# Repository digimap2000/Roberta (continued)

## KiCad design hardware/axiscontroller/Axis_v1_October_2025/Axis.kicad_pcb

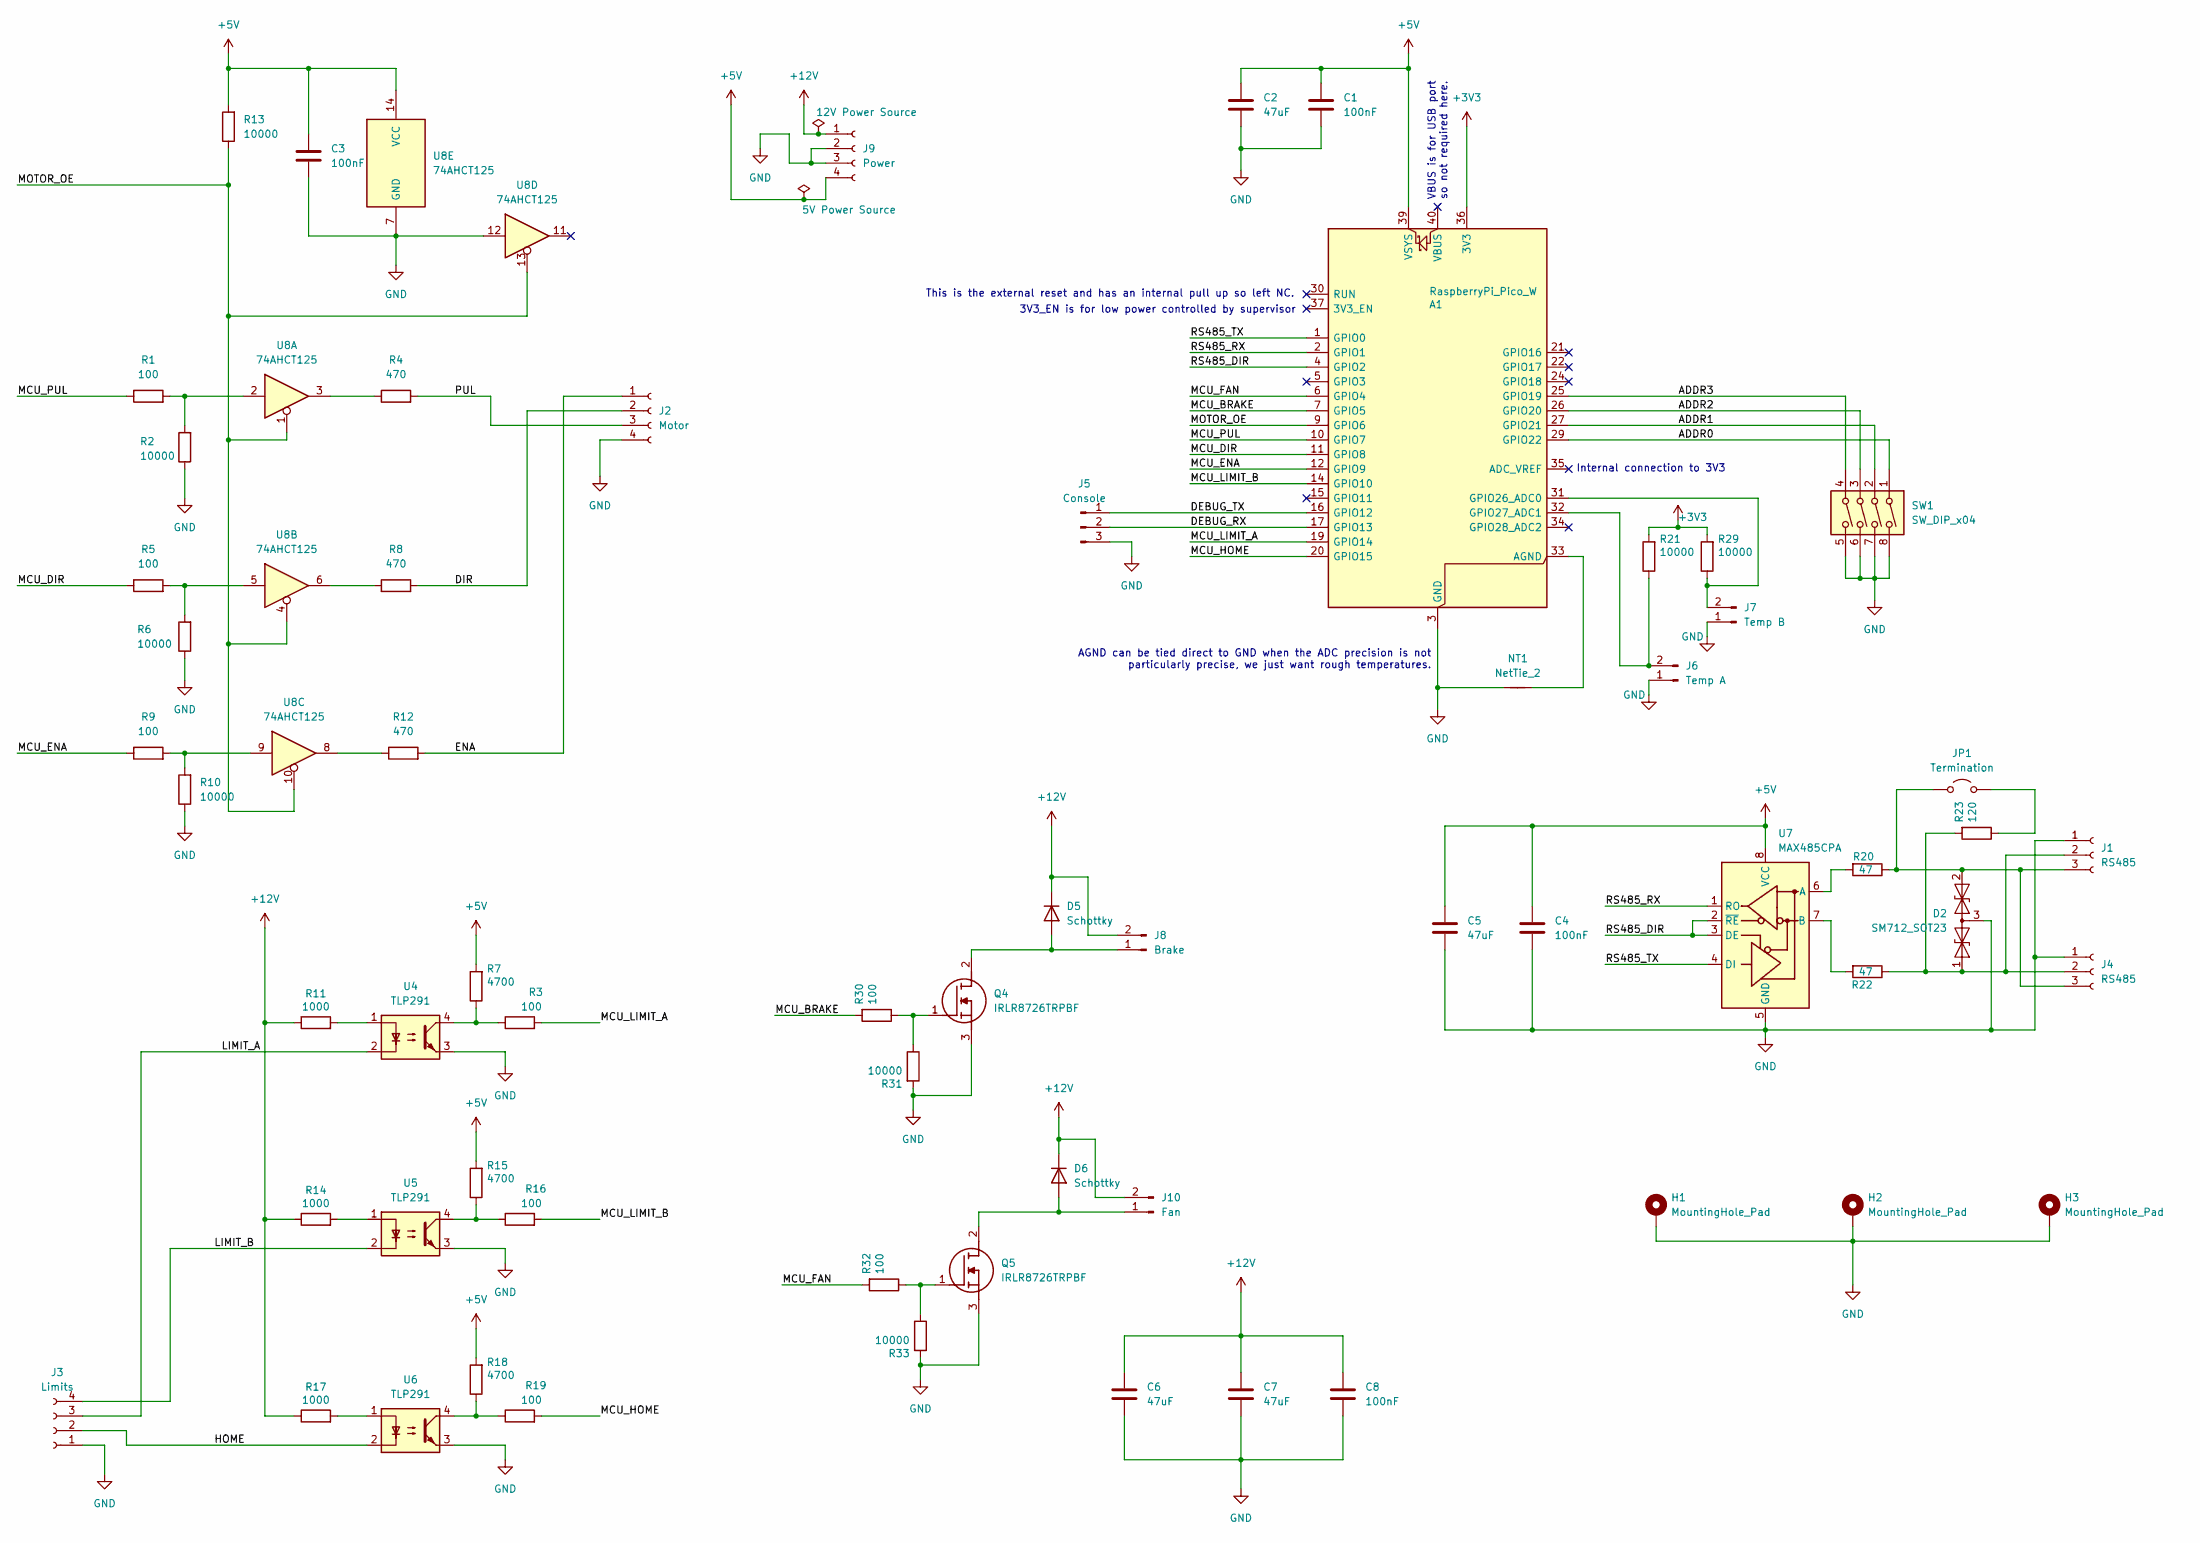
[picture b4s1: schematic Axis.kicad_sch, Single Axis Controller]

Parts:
A1: RaspberryPi_Pico_W; PI_PICO2_SOCKET
C1, C3, C4, C8: 100nF; C_0805_2012Metric; Part MC0805B104K500CT
C2, C5, C6, C7: 47uF; C_0805_2012Metric; Part GRT21BR60J476ME13L
D2: SM712_SOT23; SOT-23; Part SM712-02HTG
D5, D6: Schottky; D_SMB-SMC_Universal_Handsoldering; Part SS34
H1, H2, H3: MountingHole_Pad; MountingHole_2.2mm_M2_DIN965_Pad
J1, J4: RS485; MOLEX_SL_70553_0002; Part 70553-0002
J2: Motor; MOLEX_SL_70553_0003; Part 70553-0003
J3: Limits; MOLEX_SL_70553_0003; Part 70553-0003
J5: Console; MOLEX_SL_70553_0002; Part 70553-0002
J6: Temp A; MOLEX_SL_70553_0001; Part 70553-0001
J7: Temp B; MOLEX_SL_70553_0001; Part 70553-0001
J8: Brake; MOLEX_SL_70553_0001; Part 70553-0001
J9: Power; MOLEX-171857-0001; Part 171857-0004
J10: Fan; MOLEX_SL_70553_0001; Part 70553-0001
JP1: Termination; PinHeader_2x01_P2.54mm_Vertical
NT1: NetTie_2; NetTie-2_SMD_Pad2.0mm
Q4, Q5: IRLR8726TRPBF; Manufacturer_Part_Number IRLR8726TRPBF; Mouser Part Number 942-IRLR8726TRPBF
R1, R3, R5, R9, R16, R19, R30, R32: 100; R_0805_2012Metric_Pad1.20x1.40mm_HandSolder; Part ASC0805-100RFT5
R2, R6, R10, R13, R21, R29, R31, R33: 10000; R_0805_2012Metric_Pad1.20x1.40mm_HandSolder; Part CRGCQ0805F10K
R4, R8, R12: 470; R_0805_2012Metric_Pad1.20x1.40mm_HandSolder; Part ASC0805-470RFT5
R7, R15, R18: 4700; R_0805_2012Metric_Pad1.20x1.40mm_HandSolder; Part ASC0805-4K7FT5
R11, R14, R17: 1000; R_0805_2012Metric_Pad1.20x1.40mm_HandSolder; Part ASC0805-1K0FT5
R20, R22: 47; R_0805_2012Metric_Pad1.20x1.40mm_HandSolder; Part ASC1206-47RFT5
R23: 120; R_0805_2012Metric_Pad1.20x1.40mm_HandSolder; Part CRG0805F120R
SW1: SW_DIP_x04; DIP-8_W7.62mm; Part MCNDI-04S
U4, U5, U6: TLP291; SOIC-4_4.55x2.6mm_P1.27mm; Part TLP291(GB,SE
U7: MAX485CPA; DIP-8_W7.62mm; Part MAX485CPA+
U8: 74AHCT125; DIP-14_W7.62mm; Part SN74AHCT125N

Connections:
+3V3: A1.36 (3V3), R21.2, R29.2
+5V: A1.39 (VSYS), C1.1, C2.1, C3.1, C4.1, C5.1, J9.4, R7.2, R13.2, R15.2, R18.2, U7.8 (VCC), U8.14 (VCC)
+12V: C6.1, C7.1, C8.1, D5.1 (K), D6.1 (K), J8.2, J9.1, J10.2, R11.1, R14.1, R17.1
/ADDR0: A1.29 (GPIO22), SW1.1
/ADDR1: A1.27 (GPIO21), SW1.2
/ADDR2: A1.26 (GPIO20), SW1.3
/ADDR3: A1.25 (GPIO19), SW1.4
/DEBUG_RX: A1.17 (GPIO13), J5.2
/DEBUG_TX: A1.16 (GPIO12), J5.1
/DIR: J2.2, R8.2
/ENA: J2.1, R12.2
/HOME: J3.2, U6.2
/LIMIT_A: J3.3, U4.2
/LIMIT_B: J3.4, U5.2
/MCU_BRAKE: A1.7 (GPIO5), R30.2
/MCU_DIR: A1.11 (GPIO8), R5.1
/MCU_ENA: A1.12 (GPIO9), R9.1
/MCU_FAN: A1.6 (GPIO4), R32.2
/MCU_HOME: A1.20 (GPIO15), R19.2
/MCU_LIMIT_A: A1.19 (GPIO14), R3.2
/MCU_LIMIT_B: A1.14 (GPIO10), R16.2
/MCU_PUL: A1.10 (GPIO7), R1.1
/MOTOR_OE: A1.9 (GPIO6), R13.1, U8.1, U8.4, U8.10, U8.13
/PUL: J2.3, R4.2
/RS485_DIR: A1.4 (GPIO2), U7.2 (~RE), U7.3 (DE)
/RS485_RX: A1.2 (GPIO1), U7.1 (RO)
/RS485_TX: A1.1 (GPIO0), U7.4 (DI)
GND: A1.3 (GND), A1.8 (GND), A1.13 (GND), A1.18 (GND), A1.23 (GND), A1.28 (GND), A1.38 (GND), C1.2, C2.2, C3.2, C4.2, C5.2, C6.2, C7.2, C8.2, D2.3 (common), H1.1, H2.1, H3.1, J1.1, J2.4, J3.1, J4.1, J5.3, J6.1, J7.1, J9.2, J9.3, NT1.1, Q4.3 (S), Q5.3 (S), R2.1, R6.1, R10.1, R31.2, R33.2, SW1.5, SW1.6, SW1.7, SW1.8, U4.3, U5.3, U6.3, U7.5 (GND), U8.7 (GND), U8.12
unnamed: A1.33 (AGND), NT1.2
unnamed: A1.31 (GPIO26_ADC0), J7.2, R29.1
unnamed: A1.32 (GPIO27_ADC1), J6.2, R21.1
unnamed: D2.1 (A1), J1.2, J4.2, R22.1, R23.2
unnamed: D2.2 (A2), J1.3, J4.3, JP1.1 (A), R20.1
unnamed: D5.2 (A), J8.1, Q4.2 (D)
unnamed: D6.2 (A), J10.1, Q5.2 (D)
unnamed: JP1.2 (B), R23.1
unnamed: Q4.1 (G), R30.1, R31.1
unnamed: Q5.1 (G), R32.1, R33.1
unnamed: R1.2, R2.2, U8.2
unnamed: R3.1, R7.1, U4.4
unnamed: R4.1, U8.3
unnamed: R5.2, R6.2, U8.5
unnamed: R8.1, U8.6
unnamed: R9.2, R10.2, U8.9
unnamed: R11.2, U4.1
unnamed: R12.1, U8.8
unnamed: R14.2, U5.1
unnamed: R15.1, R16.1, U5.4
unnamed: R17.2, U6.1
unnamed: R18.1, R19.1, U6.4
unnamed: R20.2, U7.6 (A)
unnamed: R22.2, U7.7 (B)

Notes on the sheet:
AGND can be tied direct to GND when the ADC precision is not particularly precise, we just want rough temperatures.
VBUS is for USB port so not required here.
Internal connection to 3V3
3V3_EN is for low power controlled by supervisor
This is the external reset and has an internal pull up so left NC.

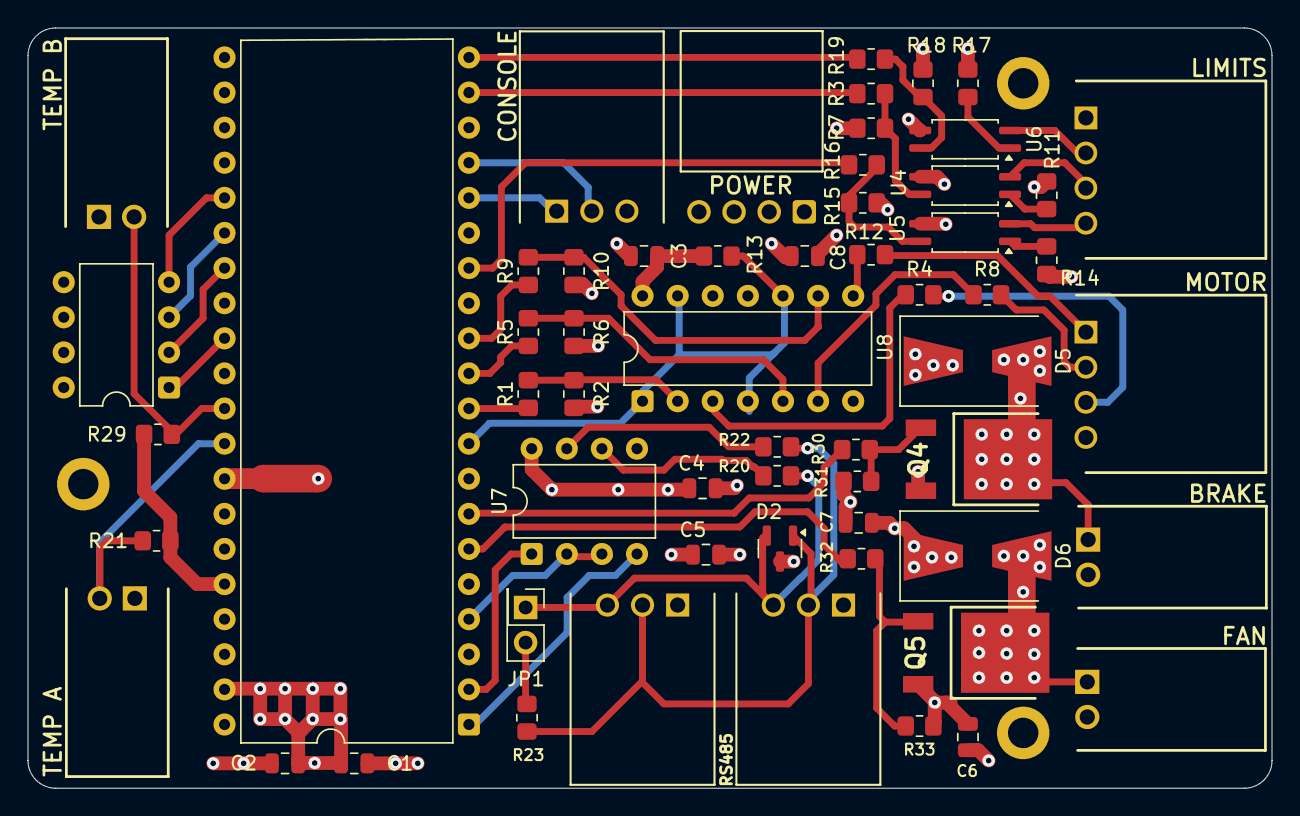
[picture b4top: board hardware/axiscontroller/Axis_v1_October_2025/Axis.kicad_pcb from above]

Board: 4 copper layers, 90.0 x 55.0 mm, 63 parts (0 on the bottom side), 52 nets.

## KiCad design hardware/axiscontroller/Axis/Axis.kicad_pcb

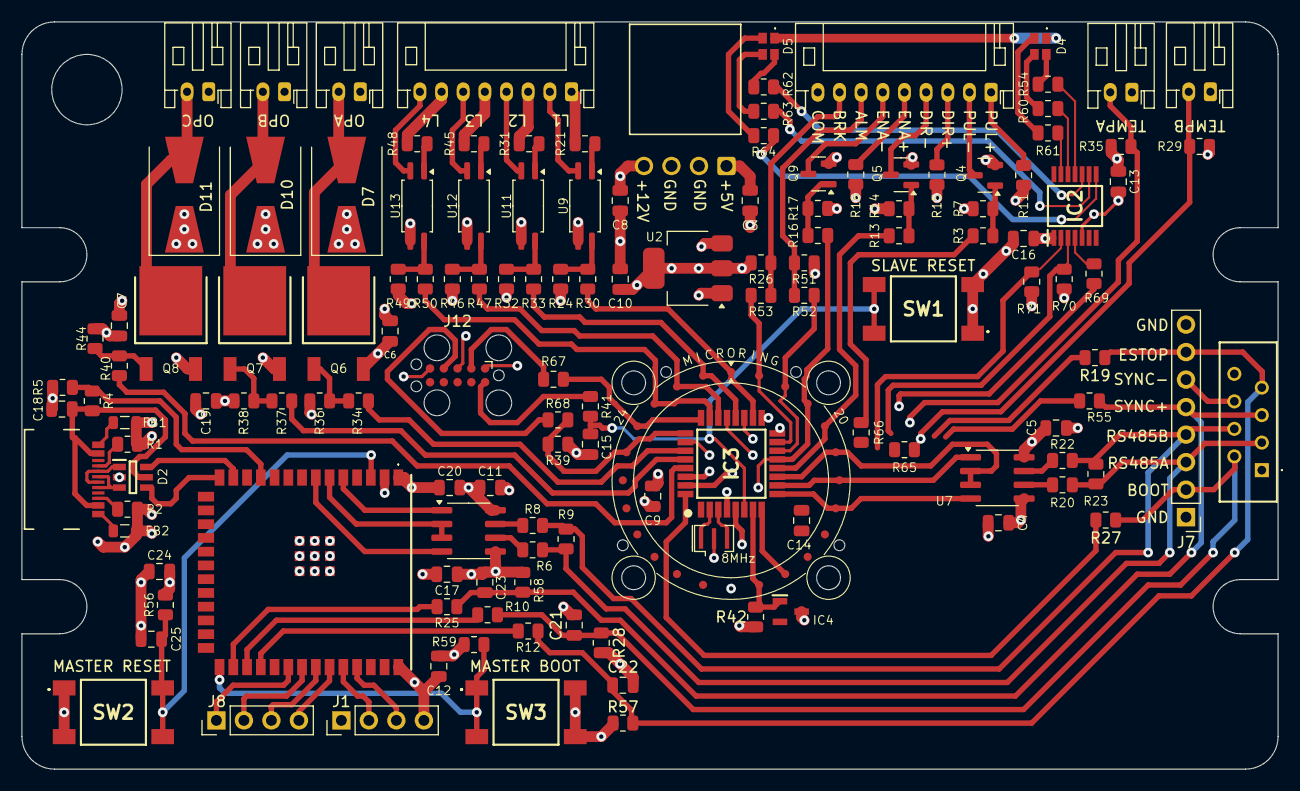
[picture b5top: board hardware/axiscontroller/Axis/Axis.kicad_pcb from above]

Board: 4 copper layers, 116.0 x 69.0 mm, 138 parts (0 on the bottom side), 114 nets.

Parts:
C3, C10: 10uF; C_0805_2012Metric
C4, C8, C9, C15, C16, C17, C18, C19, C20: 100nF; C_0805_2012Metric
C5, C6, C7, C11, C13: 47uF; C_0805_2012Metric
C12, C24: 22uF; C_0805_2012Metric
C14: 4.7uF; C_0805_2012Metric
C21, C22, C23: 22nF; C_0805_2012Metric
C25: 1uF; C_0805_2012Metric
D2: USBLC6-2SC6Y
D4, D5: CLMUD_FKC; CLMVC-FKC-CG1J1561BB7D3S3
D7, D10, D11: Schottky; D_SMB-SMC_Universal_Handsoldering
FB1, FB2: FerriteBead_Small; L_0805_2012Metric
H1: MountingHole; MountingHole_6.5mm
IC1: ESP32-S3-WROOM-1U-N16R8; ESP32-S-3WROOM-1U-N16R8
IC2: TCA6507PWR
IC3: STM32G071KBT3TR
IC4: AT21CS01-STUM10-T
J1, J8: Conn_01x04_Pin; PinHeader_1x04_P2.54mm_Vertical
J2: CL57_Driver; JST_PH_S9B-PH-K_1x09_P2.00mm_Horizontal
J3: KK254-171857-0004
J4: Conn_02x12_Counter_Clockwise; MicroRing24x20
J5: USBC-217179-0001
J6: TE MicroMatch; MicroMatch_Locking_3380708
J7: PinHeader_1x08_P2.54mm_Vertical
J12: TC2050; Tag-Connect_TC2050-IDC-FP_2x05_P1.27mm_Vertical
J17, J19, J20, J21, J22: JST PH; JST_PH_S2B-PH-K_1x02_P2.00mm_Horizontal
J18: JST PH; JST_PH_S8B-PH-K_1x08_P2.00mm_Horizontal
Q4, Q5, Q9: 2N7002; SOT-23
Q6, Q7, Q8: IRLR8726TRPBF
R1, R2: 5K1; R_0805_2012Metric
R3, R13, R16, R19, R27, R30, R33, R34, R37, R40, R41, R47, R50, R52, R53, R55: 100; R_0805_2012Metric
R4, R28, R57, R58, R70, R71: 4K7; R_0805_2012Metric
R5, R26, R39, R51: 100K; R_0805_2012Metric
R6, R8, R20, R22: 47; R_0805_2012Metric
R7, R14, R17: 100k; R_0805_2012Metric
R9, R23: 120; R_0805_2012Metric
R10, R12, R25, R65, R66, R67, R68, R69: 33; R_0805_2012Metric
R11, R15, R18: 0; R_0805_2012Metric
R21, R31, R45, R48: 1000; R_0805_2012Metric
R24, R32, R46, R49: 4700; R_0805_2012Metric
R29, R35, R36, R38, R44: 10000; R_0805_2012Metric
R42: 1K0; R_0805_2012Metric
R54, R60, R61, R62, R63, R64: 330; R_0805_2012Metric
R56, R59: R_10K; R_0805_2012Metric
SW1, SW2, SW3: SW_Tactile_6mm; Tactile_6mm_6mm_4.5mm
U2: AMS1117-3.3; SOT-223-3_TabPin2
U7, U14: MAX485CPA; SOIC-8_3.9x4.9mm_P1.27mm
U9, U11, U12, U13: TLP291; SOIC-4_4.55x2.6mm_P1.27mm
Y4: 8MHz; Resonator_SMD_Murata_CSTxExxV-3Pin_3.0x1.1mm

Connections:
+3V3: C4.1, C5.1, C9.1, C10.1, C11.1, C12.1, C13.1, C14.1, C16.1, C17.1, C19.1, C20.1, C24.1, D4.1 (A), D5.1 (A), IC1.2 (3V3), IC2.1 (VCC), IC3.4 (VDD/VDDA), J1.1, J12.1, R24.2, R26.1, R29.2, R32.2, R35.2, R42.1, R46.2, R49.2, R51.1, R56.1, R59.2, R70.1, R71.1, U2.2 (VO), U7.8 (VCC), U14.8 (VCC)
+5V: C3.1, J3.1, R11.1, R15.1, R18.1, U2.3 (VI)
+12V: C6.1, C7.1, C8.1, D7.1 (K), D10.1 (K), D11.1 (K), J3.4, J17.1, J18.1, J18.3, J18.5, J18.7, J19.1, J20.1, R21.1, R31.1, R45.1, R48.1
/ALARM: J2.7, R51.2, R52.2
/BOOT: C21.1, J6.2, J7.2, R10.2, R27.1, R28.1
/DIR+: J2.3, R15.2
/DIR-: J2.4, Q5.3 (D)
/ENA+: J2.5, R18.2
/ENA-: J2.6, Q9.3 (D)
/ESTOP: C22.1, J6.7, J7.7, R12.2, R19.1, R57.1
/INPOS: J2.8, R26.2, R53.2
/LIMIT_A: IC3.18 (PA8), J4.1, R30.2
/LIMIT_B: IC3.20 (PC6), J4.2, R33.2
/LIMIT_C: IC3.22 (PA11_[PA9]), J4.3, R47.2
/LIMIT_D: IC3.23 (PA12_[PA10]), J4.4, R50.2
/MCU_DIR: IC3.12 (PA5), J4.21, R13.1
/MCU_ENA: IC3.13 (PA6), J4.22, R16.1
/MCU_PUL: IC3.30 (PB6), R3.1
/Master/CONSOLE_RX: IC1.36 (RXD0), J1.2
/Master/CONSOLE_TX: IC1.37 (TXD0), J1.3
/Master/ESP32_BOOT: IC1.27 (IO0), R59.1, SW3.1
/Master/MCU_BOOT: IC1.29 (IO36), R10.1
/Master/MCU_ESTOP: IC1.30 (IO37), R12.1
/Master/MCU_SYNC: IC1.28 (IO35), R25.1
/Master/TCK: IC1.32 (IO39), J8.1
/Master/TDI: IC1.34 (IO41), J8.3
/Master/TDO: IC1.33 (IO40), J8.2
/Master/TMS: IC1.35 (IO42), J8.4
/Master/USB_D+: D2.4 (I/O2_2), IC1.14 (IO20)
/Master/USB_D-: D2.6 (I/O1_2), IC1.13 (IO19)
/Master/USB_SENSE: IC1.11 (IO18), R4.2, R5.1
/MicroController/BOOT: IC3.32 (PB8), R27.2
/MicroController/ESTOP: IC3.31 (PB7), J4.16, R19.2
/MicroController/LED_OE: IC2.4 (EN), R69.1
/MicroController/MCU_SCL: IC3.19 (PA9), R66.2
/MicroController/MCU_SDA: IC3.21 (PA10), R65.2
/MicroController/MCU_SWDCLK: IC3.25 (PA14-BOOT0), J4.6, R39.1, R68.2
/MicroController/MCU_SWDIO: IC3.24 (PA13), J4.5, R67.2
/MicroController/MOTOR_ALARM: IC3.14 (PA7), J4.23, R52.1
/MicroController/MOTOR_INPOS: IC3.15 (PB0), J4.24, R53.1
/MicroController/NRST: C15.1, IC3.6 (PF2-NRST), R41.2, SW1.2
/MicroController/OSCX_IN: IC3.2 (PC14-OSC32_IN), Y4.1
/MicroController/OSCX_OUT: IC3.3 (PC15-OSC32_OUT), Y4.3
/MicroController/RS485_DIR: IC3.11 (PA4), J4.20, U7.2 (~RE), U7.3 (DE)
/MicroController/RS485_RX: IC3.10 (PA3), J4.19, U7.1 (RO)
/MicroController/RS485_TX: IC3.9 (PA2), J4.18, U7.4 (DI)
/MicroController/SCL: IC2.2 (SCL), R66.1, R71.2
/MicroController/SDA: IC2.3 (SDA), R65.1, R70.2
/MicroController/SIO: IC3.7 (PA0), IC4.1 (SI/O), J4.14, R42.2
/MicroController/SWDCLK/BOOT: J12.4, R68.1
/MicroController/SWDIO: J12.2, R67.1
/MicroController/SWDRST: J12.10, R41.1
/MicroController/SYNC: IC3.8 (PA1), J4.15, R55.2
/MicroController/TEMP_A: IC3.17 (PB2), J21.2, R35.1
/MicroController/TEMP_B: IC3.16 (PB1), J22.2, R29.1
/OP_BRAKE: IC3.28 (PB4), R37.2
/OP_FAN: IC3.27 (PB3), R34.2
/OP_SPARE: IC3.29 (PB5), R40.2
/Opto Input 1/SWITCH-: J18.2, U9.2
/Opto Input 2/SWITCH-: J18.4, U11.2
/Opto Input 3/SWITCH-: J18.6, U12.2
/Opto Input 4/SWITCH-: J18.8, U13.2
/PUL+: J2.1, R11.2
/PUL-: J2.2, Q4.3 (D)
/Power Output A/Load-: D7.2 (A), J19.2, Q6.2 (D)
/Power Output B/Load-: D10.2 (A), J17.2, Q7.2 (D)
/Power Output C/Load-: D11.2 (A), J20.2, Q8.2 (D)
/RS485_A: J6.3, J7.3, R6.1, R9.1, R20.1, R23.1
/RS485_B: J6.4, J7.4, R8.1, R9.2, R22.1, R23.2
/SYNC: C23.1, J6.5, J7.5, R25.2, R55.1, R58.1
GND: C3.2, C4.2, C5.2, C6.2, C7.2, C8.2, C9.2, C10.2, C11.2, C12.2, C13.2, C14.2, C15.2, C16.2, C17.2, C18.2, C19.2, C20.2, C21.2, C22.2, C23.2, C24.2, C25.2, D2.2 (GND), FB1.2, FB2.2, IC1.1 (GND_1), IC1.40 (GND_2), IC1.41 (GND_3), IC1.42 (GND_4), IC1.43 (GND_5), IC1.44 (GND_6), IC1.45 (GND_7), IC1.46 (GND_8), IC1.47 (GND_9), IC1.48 (GND_10), IC1.49 (GND_11), IC2.5 (GND), IC3.5 (VSS/VSSA), IC4.3 (GND), J1.4, J2.9, J3.2, J3.3, J4.13, J6.1, J6.8, J7.1, J7.8, J12.3, J12.5, J21.1, J22.1, Q4.2 (S), Q5.2 (S), Q6.3 (S), Q7.3 (S), Q8.3 (S), Q9.2 (S), R1.2, R2.2, R5.2, R7.1, R14.1, R17.1, R28.2, R36.2, R38.2, R39.2, R44.2, R57.2, R58.2, SW1.1, SW2.1, SW3.2, U2.1 (GND), U7.5 (GND), U9.3, U11.3, U12.3, U13.3, U14.5 (GND), Y4.2
unnamed: D2.1 (I/O1_1), J5.A7 (DN1), J5.B7 (DN2)
unnamed: D2.3 (I/O2_1), J5.A6 (DP1), J5.B6 (DP2)
unnamed: C18.1, D2.5 (VBUS), J5.A4/B9 (VBUS), J5.B4/A9 (VBUS), R4.1
unnamed: D4.4 (BK), R61.2
unnamed: D4.3 (GK), R60.2
unnamed: D4.2 (RK), R54.2
unnamed: D5.4 (BK), R64.2
unnamed: D5.3 (GK), R63.2
unnamed: D5.2 (RK), R62.2
unnamed: FB1.1, J5.A1/B12 (GND)
unnamed: FB2.1, J5.B1/A12 (GND)
unnamed: C25.1, IC1.3 (EN), R56.2, SW2.2
unnamed: IC1.5 (IO5), U14.1 (RO)
unnamed: IC1.6 (IO6), U14.2 (~RE), U14.3 (DE)
unnamed: IC1.7 (IO7), U14.4 (DI)
unnamed: IC2.8 (P0), R64.1
unnamed: IC2.9 (P1), R63.1
unnamed: IC2.10 (P2), R62.1
unnamed: IC2.11 (P3), R54.1
unnamed: IC2.12 (P4), R60.1
unnamed: IC2.13 (P5), R61.1
unnamed: IC3.26 (PA15), R69.2
unnamed: J5.A5 (CC1), R1.1
unnamed: J5.B5 (CC2), R2.1
unnamed: J6.6, J7.6
unnamed: Q4.1 (G), R3.2, R7.2
unnamed: Q5.1 (G), R13.2, R14.2
unnamed: Q6.1 (G), R34.1, R36.1
unnamed: Q7.1 (G), R37.1, R38.1
unnamed: Q8.1 (G), R40.1, R44.1
unnamed: Q9.1 (G), R16.2, R17.2
unnamed: R21.2, U9.1
unnamed: R24.1, R30.1, U9.4
unnamed: R31.2, U11.1
unnamed: R32.1, R33.1, U11.4
unnamed: R45.2, U12.1
unnamed: R46.1, R47.1, U12.4
unnamed: R48.2, U13.1
unnamed: R49.1, R50.1, U13.4
unnamed: R20.2, U7.6 (A)
unnamed: R22.2, U7.7 (B)
unnamed: R6.2, U14.6 (A)
unnamed: R8.2, U14.7 (B)

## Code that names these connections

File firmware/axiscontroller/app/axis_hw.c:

#include "axis_hw.h"

#include "pico/stdlib.h"

enum {
    GPIO_FAN = 4,
    GPIO_BRAKE = 5,
    GPIO_MOTOR_OE = 6,
    GPIO_MOTOR_PUL = 7,
    GPIO_MOTOR_DIR = 8,
    GPIO_MOTOR_ENA = 9,
    GPIO_LIMIT_B = 10,
    DE_RE_PIN = 2,
    GPIO_LIMIT_A = 14,
    GPIO_LIMIT_HOME = 15,
};

static const bool k_output_enable_active_level = false;
static const bool k_motor_enable_active_level = false;
static const bool k_step_active_level = false;
static const bool k_fan_active_level = true;
static const bool k_brake_active_level = true;

static AxisOutputState g_outputs = {
    .outputs_enabled = false,
    .motor_enabled = false,
    .direction = AXIS_DIRECTION_POSITIVE,
    .step_active = false,
    .fan_active = false,
    .brake_active = false,
};

static void init_output_pin(uint pin, bool initial_level)
{
    gpio_init(pin);
    gpio_set_dir(pin, GPIO_OUT);
    gpio_put(pin, initial_level);
}

static void init_input_pin(uint pin)
{
    gpio_init(pin);
    gpio_set_dir(pin, GPIO_IN);
    gpio_pull_up(pin);
}

static bool level_for_enable(bool enabled, bool active_level)
{
    return enabled ? active_level : !active_level;
}

void axis_hw_init(void)
{
    init_output_pin(DE_RE_PIN, 0);
    init_output_pin(GPIO_MOTOR_OE, !k_output_enable_active_level);
    init_output_pin(GPIO_MOTOR_PUL, !k_step_active_level);
    init_output_pin(GPIO_MOTOR_DIR, 0);
    init_output_pin(GPIO_MOTOR_ENA, !k_motor_enable_active_level);
    init_output_pin(GPIO_FAN, !k_fan_active_level);
    init_output_pin(GPIO_BRAKE, !k_brake_active_level);

    init_input_pin(GPIO_LIMIT_HOME);
    init_input_pin(GPIO_LIMIT_A);
    init_input_pin(GPIO_LIMIT_B);
}

void axis_hw_set_output_enable(bool enabled)
{
    g_outputs.outputs_enabled = enabled;
    gpio_put(GPIO_MOTOR_OE, level_for_enable(enabled, k_output_enable_active_level));
}

void axis_hw_set_motor_enable(bool enabled)
{
    g_outputs.motor_enabled = enabled;
    gpio_put(GPIO_MOTOR_ENA, level_for_enable(enabled, k_motor_enable_active_level));
}

void axis_hw_set_direction(AxisDirection direction)
{
    g_outputs.direction = direction;
    gpio_put(GPIO_MOTOR_DIR, direction == AXIS_DIRECTION_POSITIVE);
}

void axis_hw_step_pulse_start(void)
{
    g_outputs.step_active = true;
    gpio_put(GPIO_MOTOR_PUL, k_step_active_level);
}

void axis_hw_step_pulse_end(void)
{
    g_outputs.step_active = false;
    gpio_put(GPIO_MOTOR_PUL, !k_step_active_level);
}

void axis_hw_set_fan(bool enabled)
{
    g_outputs.fan_active = enabled;
    gpio_put(GPIO_FAN, level_for_enable(enabled, k_fan_active_level));
}

void axis_hw_set_brake(bool enabled)
{
    g_outputs.brake_active = enabled;
    gpio_put(GPIO_BRAKE, level_for_enable(enabled, k_brake_active_level));
}

AxisLimitState axis_hw_read_limits(void)
{
    AxisLimitState limits = {
        .home = gpio_get(GPIO_LIMIT_HOME) == 0,
        .limit_a = gpio_get(GPIO_LIMIT_A) == 0,
        .limit_b = gpio_get(GPIO_LIMIT_B) == 0,
    };
    return limits;
}

AxisOutputState axis_hw_get_output_state(void)
{
    return g_outputs;
}

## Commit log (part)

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2025-10-09 Mechanica
2025-10-09 Roberta - Single Axis Controller
2025-10-09 Remove component copies.
2025-10-09 Release date on schematic
2025-10-09 Remove backup zip file from git.
2025-10-09 Fix ERC warnings/errors and add IRLR8726 component.
2025-11-03 Adding TMC Motor Control.
2025-11-27 Experiments with the TMC2209 motor controller.
2025-11-27 Pushing last changes to roberta kicad libs before moving over to central kicad libs.
2025-11-27 More axis firmware.
2025-11-27 The second revision of the robot axis controller.
2025-11-27 Serial Monitor PCB.
2025-11-27 Wireless motor idea.
2025-11-27 URDF descriptions of Comau NS16
2025-12-20 Routing tests in copper.
2025-12-20 ratsnesting
2025-12-23 Layer parsing
2025-12-26 kicad
2025-12-27 Runtime pad model using GLM.
2026-02-14 Update dispatch_to contract
2026-03-14 Revive axis controller baseline and split protocol docs
2026-03-14 Add axis controller register bank and console API
2026-03-15 software: T01 inventory DTS and software assets
2026-03-15 software: T02 establish build and test baseline
2026-03-15 software: T03 add error and logging conventions
2026-03-15 software: record Phase 0 task hashes
2026-03-15 software: add host-side robot control vertical slice
2026-03-15 software: add ninja presets and tidy build flow
2026-03-15 Harden axis controller comms and add HIL regression tests
2026-03-15 Harden axis controller register and console paths
2026-03-25 Commit workspace updates
2026-03-25 Add text overlay rendering to pendant
2026-03-25 Improve pendant robot materials
2026-03-25 Simplify pendant environment backdrop
2026-03-25 Add pendant joint focus annotations
2026-03-25 Add local ignore rules
2026-03-26 Add Pico 2 keypad bridge firmware
2026-03-26 Reduce keypad bridge power usage
